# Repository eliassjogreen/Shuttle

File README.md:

# Shuttle
🚀 Shuttle 3x4 12 key numpad

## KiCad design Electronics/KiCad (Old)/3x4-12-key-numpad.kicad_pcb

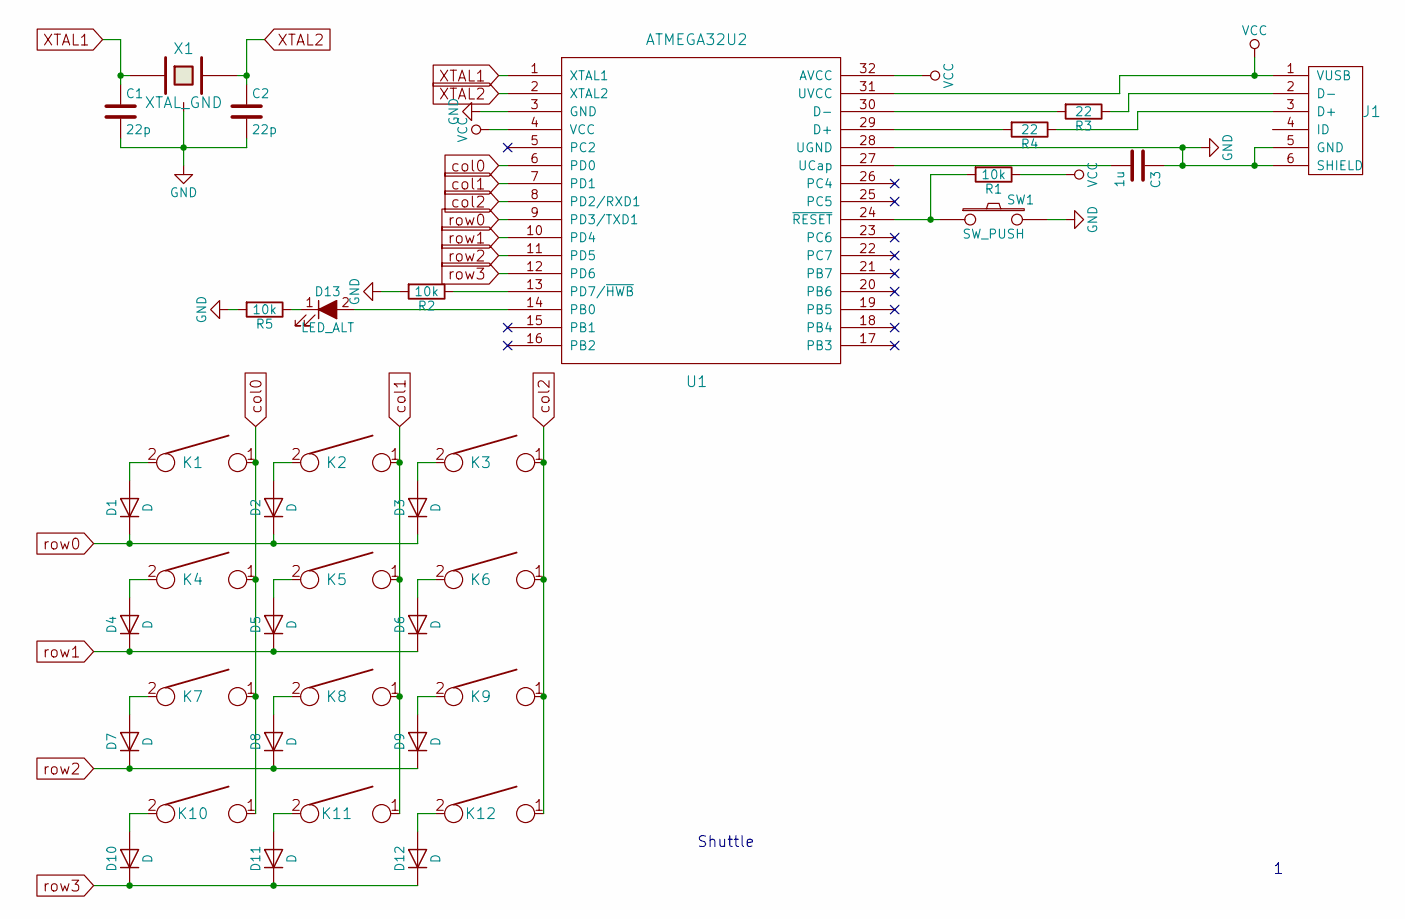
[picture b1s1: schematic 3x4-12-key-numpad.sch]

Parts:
C1, C2: 22p; C_0805_HandSoldering
C3: 1u; C_0805_HandSoldering
D1, D2, D3, D4, D5, D6, D7, D8, D9, D10, D11, D12: D; D_SOD123_axial
D13: LED_ALT; LED_0805_HandSoldering
J1: USB_mini_micro_B; USB_miniB_hirose_5S8
K1, K2, K3, K4, K5, K6, K7, K8, K9, K10, K11, K12: KEYSW; Mx_Alps_100
R1, R2, R5: 10k; R_0805_HandSoldering
R3, R4: 22; R_0805_HandSoldering
SW1: SW_PUSH; SW_SPST_TL3342
U1: ATMEGA32U2; TQFP-44_10x10mm_Pitch0.8mm
X1: XTAL_GND; Crystal_SMD_SeikoEpson_FA238-4pin_3.2x2.5mm

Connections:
GND: C1.2, C2.2, C3.1, J1.5 (GND), J1.6 (SHIELD), R2.2, R5.2, SW1.2, U1.3 (GND), U1.28 (UGND), X1.3
unnamed: C3.2, U1.27 (UCap)
unnamed: D1.2 (A), K1.2
unnamed: D2.2 (A), K2.2
unnamed: D3.2 (A), K3.2
unnamed: D4.2 (A), K4.2
unnamed: D5.2 (A), K5.2
unnamed: D6.2 (A), K6.2
unnamed: D7.2 (A), K7.2
unnamed: D8.2 (A), K8.2
unnamed: D9.2 (A), K9.2
unnamed: D10.2 (A), K10.2
unnamed: D11.2 (A), K11.2
unnamed: D12.2 (A), K12.2
unnamed: D13.1 (K), R5.1
unnamed: D13.2 (A), U1.14 (PB0)
unnamed: J1.2 (D-), R3.1
unnamed: J1.3 (D+), R4.1
unnamed: R1.2, SW1.1, U1.24 (~RESET)
unnamed: R2.1, U1.13 (PD7/~HWB)
unnamed: R3.2, U1.30 (D-)
unnamed: R4.2, U1.29 (D+)
VCC: J1.1 (VUSB), R1.1, U1.4 (VCC), U1.31 (UVCC), U1.32 (AVCC)
XTAL1: C1.1, U1.1 (XTAL1), X1.1
XTAL2: C2.1, U1.2 (XTAL2), X1.2
col0: K1.1, K4.1, K7.1, K10.1, U1.6 (PD0)
col1: K2.1, K5.1, K8.1, K11.1, U1.7 (PD1)
col2: K3.1, K6.1, K9.1, K12.1, U1.8 (PD2/RXD1)
row0: D1.1 (K), D2.1 (K), D3.1 (K), U1.9 (PD3/TXD1)
row1: D4.1 (K), D5.1 (K), D6.1 (K), U1.10 (PD4)
row2: D7.1 (K), D8.1 (K), D9.1 (K), U1.11 (PD5)
row3: D10.1 (K), D11.1 (K), D12.1 (K), U1.12 (PD6)

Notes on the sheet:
Shuttle

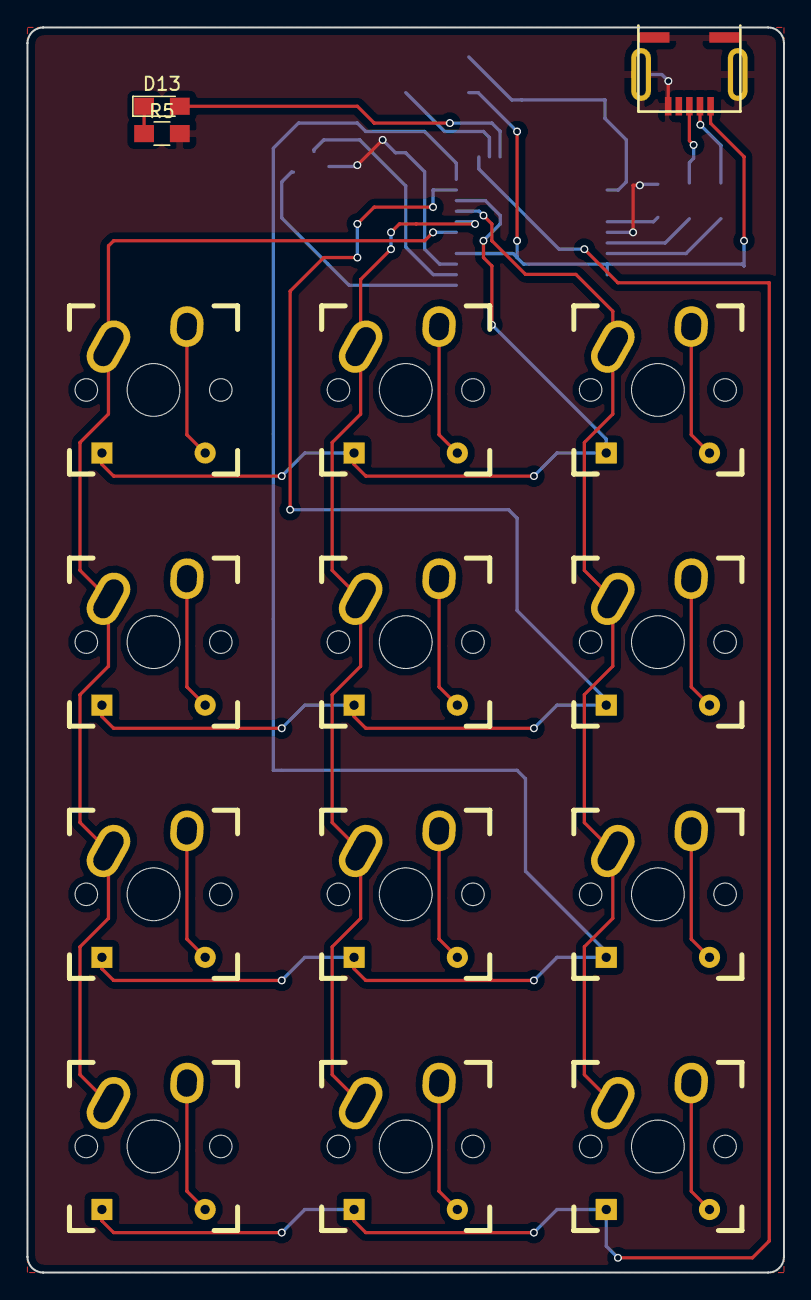
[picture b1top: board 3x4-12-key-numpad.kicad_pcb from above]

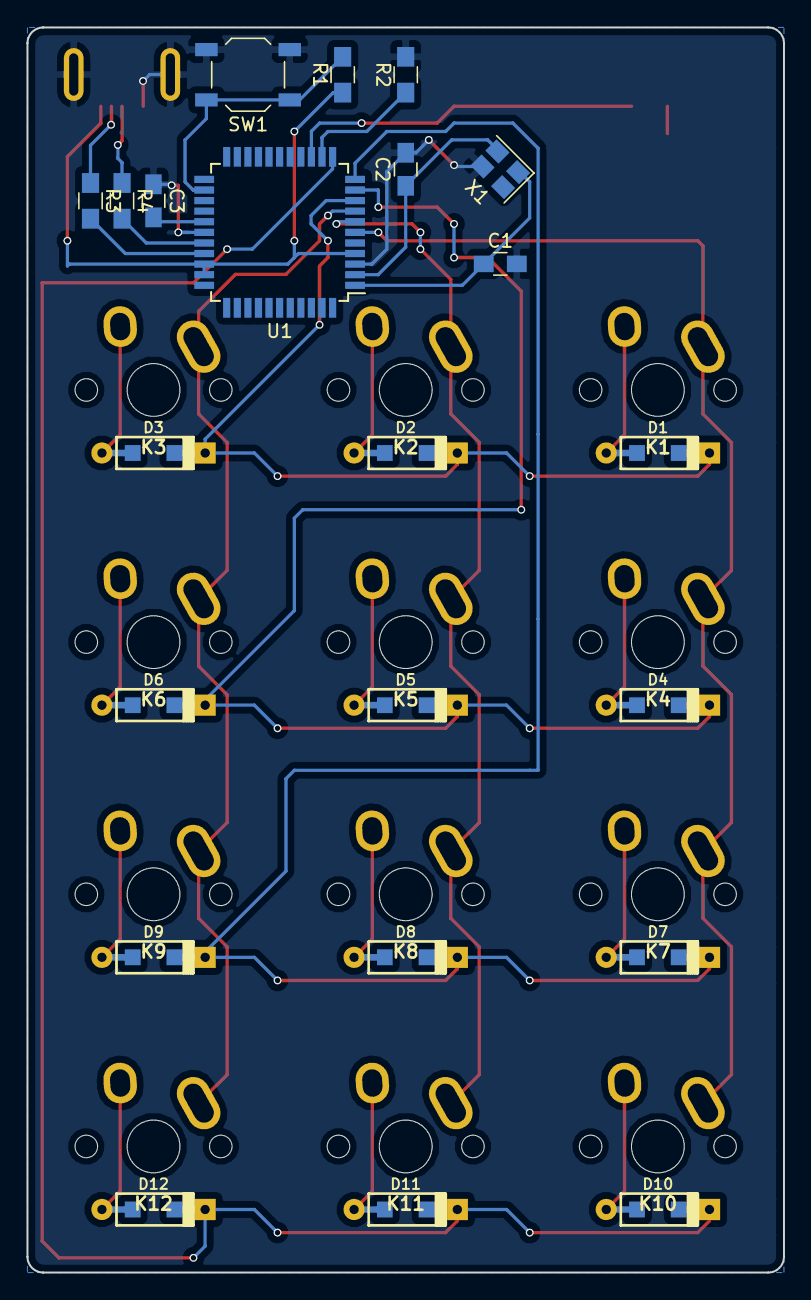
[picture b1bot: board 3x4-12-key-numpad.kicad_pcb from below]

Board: 2 copper layers, 57.2 x 94.1 mm, 37 parts (22 on the bottom side), 32 nets.

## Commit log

2017-10-10 Added images
2017-10-24 Added top plates for prototyping
2017-10-31 Added images and blender models
2017-11-03 Create LICENSE
